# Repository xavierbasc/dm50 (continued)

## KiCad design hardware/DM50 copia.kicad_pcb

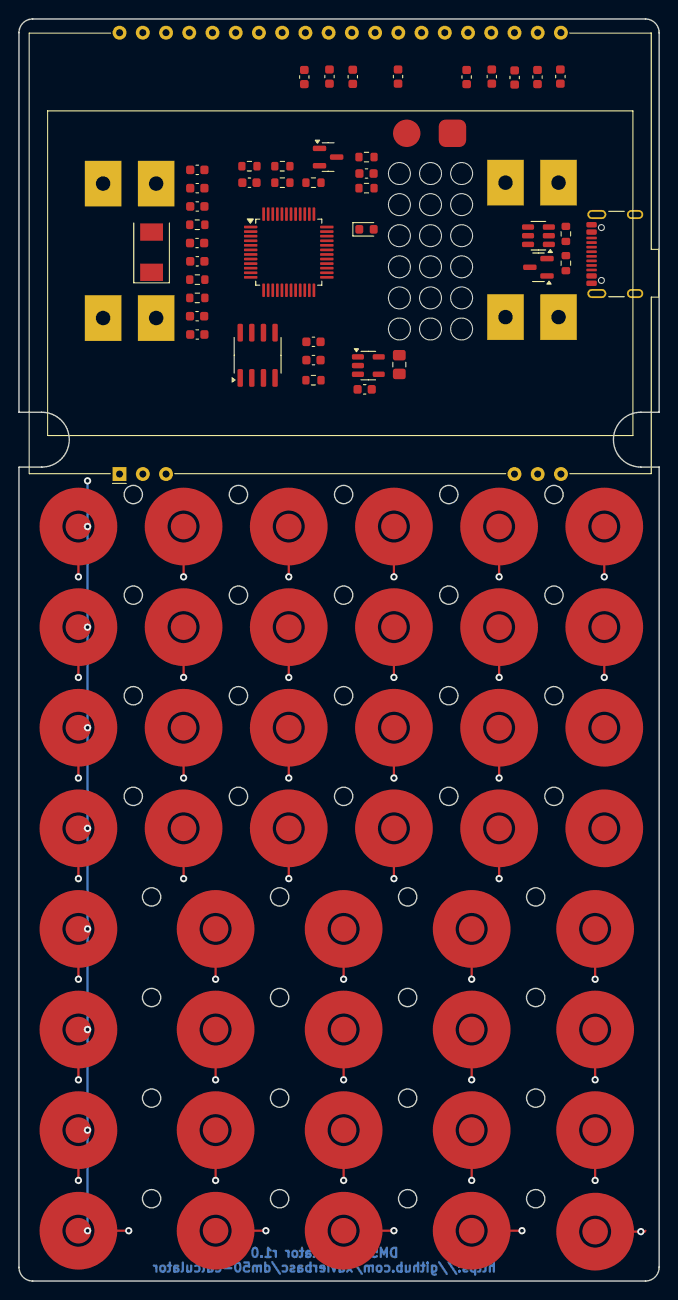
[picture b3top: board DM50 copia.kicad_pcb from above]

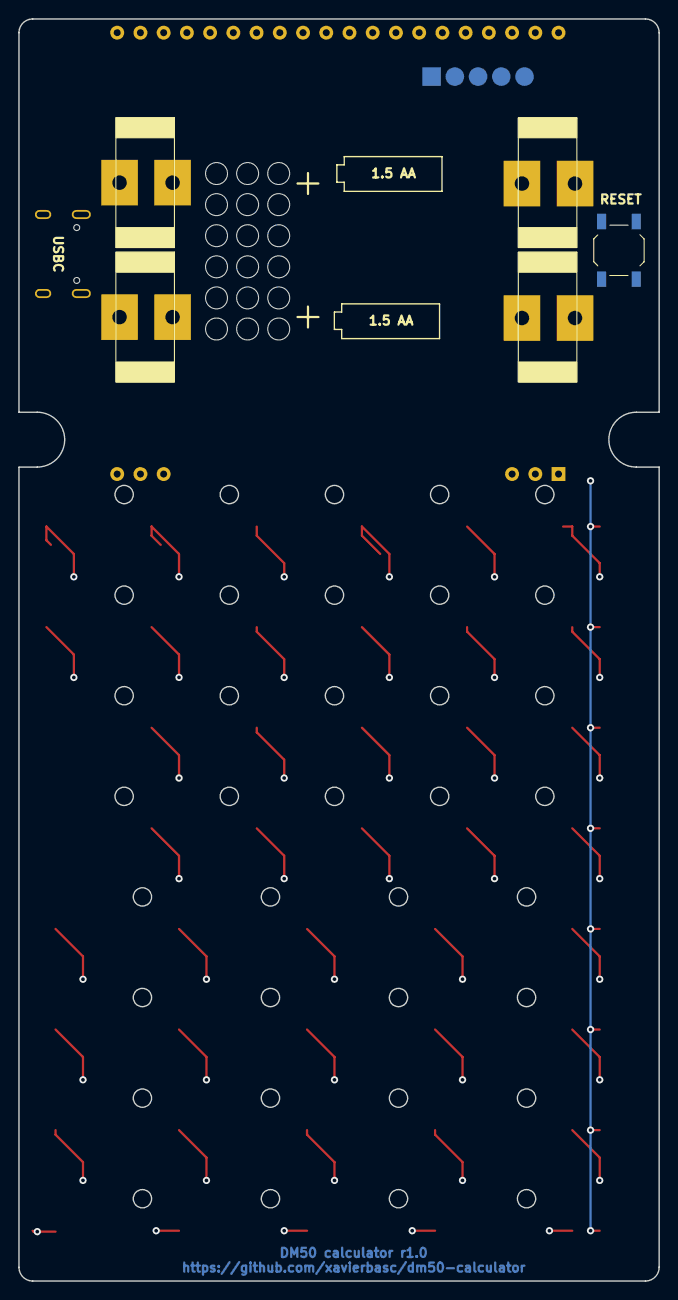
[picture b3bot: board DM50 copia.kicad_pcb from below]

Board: 2 copper layers, 70.0 x 138.0 mm, 93 parts (4 on the bottom side), 63 nets.

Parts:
BT1, BT2: AA; dm50-batAA
BZ1: Buzzer
C1, C2, C3, C4, C5, C6, C7, C8, C9: 1uF; C_0603_1608Metric
C10, C12, C14, C15, C16, C17: 100nF; C_0603_1608Metric
C11, C13: 22pF; C_0603_1608Metric
C18, C20: 4.7 uF; C_0603_1608Metric
C19: 10 uF; C_0603_1608Metric
C21: 2.2uF; C_0603_1608Metric
D1: LED (RED); LED_0603_1608Metric
D2: BAT54C; SOT-23
J1: ST-LINK; JST_CON_SMD
J2: USB_C_Receptacle_USB2.0_14P; USB_C_Receptacle_GCT_USB4105-xx-A_16P_TopMnt_Horizontal
L1: 1uH; L_0805_2012Metric_Pad1.15x1.40mm_HandSolder
Q1: MMBT3904; SOT-23
R1: 10k; R_0603_1608Metric
R2, R10, R11: 5.1K; R_0603_1608Metric
R3, R6: 1M; R_0603_1608Metric
R4, R12: 10K; R_0603_1608Metric
R5, R7: 100K; R_0603_1608Metric
R8, R9: R; R_0603_1608Metric
SW1: F1; dm50-button
SW2: F2; dm50-button
SW3: F3; dm50-button
SW4: F4; dm50-button
SW5: F5; dm50-button
SW6: F6; dm50-button
SW7: E+; dm50-button
SW8: 1/x; dm50-button
SW9: SQR; dm50-button
SW10: LOG; dm50-button
SW11: LN; dm50-button
SW12: XEQ; dm50-button
SW13: STO; dm50-button
SW14: RCL; dm50-button
SW15: R; dm50-button
SW16: SIN; dm50-button
SW17: COS; dm50-button
SW18: TAN; dm50-button
SW19, SW20: ENTER; dm50-button
SW21: x<>y; dm50-button
SW22: +/-; dm50-button
SW23: E; dm50-button
SW24: DEL; dm50-button
SW25: UP; dm50-button
SW26: 7; dm50-button
SW27: 8; dm50-button
SW28: 9; dm50-button
SW29: /; dm50-button
SW30: DOWN; dm50-button
SW31: 4; dm50-button
SW32: 5; dm50-button
SW33: 6; dm50-button
SW34: x; dm50-button
SW35: OPT; dm50-button
SW36: 1; dm50-button
SW37: 2; dm50-button
SW38: 3; dm50-button
SW39: -; dm50-button
SW40: ON; dm50-button
SW41: 0; dm50-button
SW42: .; dm50-button
SW43: =; dm50-button
SW44: +; dm50-button
SW45: SW_RESET; SW_SPST_TL3342
U1: EA_DOGL128X-6; EA_DOGL128-6
U2: STM32U535CBT6; LQFP-48_7x7mm_P0.5mm
U3: AT25SF641; SOIC-8_3.9x4.9mm_P1.27mm
U4: USBLC6-2SC6; SOT-23-6
U5: ADP2108AUJ-3.3; TSOT-23-5
Y1: HSE 16MHz; Crystal_SMD_0603-2Pin_6.0x3.5mm

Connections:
3.3V: BZ1.1 (+), C14.1, C15.1, C16.1, C17.1, C18.1, C19.1, L1.2, R1.1, R4.2, R8.1, U1.34 (VDD2), U1.35 (VDD), U2.1 (VBAT), U2.9 (VDDA), U2.24 (VDD), U2.36 (VDD), U2.48 (VDD), U3.8 (VCC), U5.4 (FB)
BOOT0: R7.2, SW30.2, SW31.2, SW32.2, SW33.2, SW34.2, U2.44 (PH3)
BUZZER: R9.1, U2.42 (PB6)
COL01: SW1.1, SW7.1, SW13.1, SW19.1, SW25.1, SW30.1, SW35.1, SW40.1, U2.3 (PC14)
COL02: R4.1, SW2.1, SW8.1, SW14.1, SW20.1, SW26.1, SW31.1, SW36.1, SW41.1, U2.40 (PB4)
COL03: SW3.1, SW9.1, SW15.1, SW21.1, SW27.1, SW32.1, SW37.1, SW42.1, U2.30 (PA9)
COL04: SW4.1, SW10.1, SW16.1, SW22.1, SW28.1, SW33.1, SW38.1, SW43.1, U2.20 (PB2)
COL05: SW5.1, SW11.1, SW17.1, SW23.1, SW29.1, SW34.1, SW39.1, SW44.1, U2.29 (PA8)
COL06: SW6.1, SW12.1, SW18.1, SW24.1, U2.38 (PA15)
DISP_A0: U1.38 (A0), U2.14 (PA4)
DISP_CS1B: U1.40 (~CS1B), U2.15 (PA5)
DISP_RST: U1.39 (~RST), U2.31 (PA10)
DISP_SCL: U1.37 (SCL), U2.12 (PA2)
DISP_SI: U1.36 (SI), U2.43 (PB7)
GND: BT2.2 (-), C1.2, C2.2, C3.2, C5.2, C6.2, C8.1, C10.2, C11.2, C12.2, C13.2, C14.2, C15.2, C16.2, C17.2, C18.2, C19.2, C20.2, C21.2, D1.1 (K), J1.1, J2.A1 (GND), J2.A12 (GND), J2.B1 (GND), J2.B12 (GND), J2.S1 (SHIELD), Q1.2 (E), R5.2, R6.1, R7.1, R10.2, R11.2, SW45.1, U1.26 (VSS), U1.33 (VSS), U2.8 (VSSA), U2.23 (VSS), U2.35 (VSS), U2.47 (VSS), U3.4 (GND), U4.2 (GND), U5.2 (GND)
LED01: R2.1, U2.41 (PB5)
NRST: C10.1, J1.5, R1.2, U2.7 (NRST)
unnamed: BT1.2 (-), BT2.1 (+)
unnamed: BZ1.2 (-), Q1.3 (C), R8.2
unnamed: D1.2 (A), R2.2
unnamed: J2.A5 (CC1), R10.1
unnamed: J2.B5 (CC2), R11.1
unnamed: J2.A6 (D+), J2.B6 (D+), U4.3 (I/O2)
unnamed: J2.A7 (D-), J2.B7 (D-), U4.1 (I/O1)
unnamed: Q1.1 (B), R9.2
unnamed: C4.2, C7.2, U1.30 (CAP1N)
unnamed: C4.1, U1.29 (CAP1P)
unnamed: C9.1, U1.27 (CAP2N)
unnamed: C9.2, U1.28 (CAP2P)
unnamed: C7.1, U1.31 (CAP3P)
unnamed: C1.1, U1.21 (V0)
unnamed: C2.1, U1.22 (V1)
unnamed: C3.1, U1.23 (V2)
unnamed: C5.1, U1.24 (V3)
unnamed: C6.1, U1.25 (V4)
unnamed: C8.2, U1.32 (VOUT)
unnamed: D2.2, J2.A4 (VBUS), J2.A9 (VBUS), J2.B4 (VBUS), J2.B9 (VBUS), U4.5 (VBUS)
unnamed: R12.2, SW45.2, U5.3 (EN)
unnamed: L1.1, U5.5 (SW)
unnamed: C20.1, D2.3, R12.1, U5.1 (Vin)
OSCIN: C11.1, U2.5 (PH0), Y1.2
OSCOUT: C13.1, U2.6 (PH1), Y1.1
QUADSPI_CLK: U2.13 (PA3), U3.6 (CLK)
QUADSPI_IO0: U2.19 (PB1), U3.5 (DI(IO0))
QUADSPI_IO1: U2.18 (PB0), U3.2 (DO(IO1))
QUADSPI_IO2: U2.17 (PA7), U3.3 (IO2)
QUADSPI_IO3: U2.16 (PA6), U3.7 (IO3)
QUADSPI_NCS: U2.10 (PA0), U3.1 (~CS)
ROW01: SW1.2, SW2.2, SW3.2, SW4.2, SW5.2, SW6.2, U2.26 (PB13)
ROW02: SW7.2, SW8.2, SW9.2, SW10.2, SW11.2, SW12.2, U2.45 (PB8)
ROW03: SW13.2, SW14.2, SW15.2, SW16.2, SW17.2, SW18.2, U2.46 (PB9)
ROW04: SW19.2, SW20.2, SW21.2, SW22.2, SW23.2, SW24.2, U2.21 (PB10)
ROW05: SW25.2, SW26.2, SW27.2, SW28.2, SW29.2, U2.25 (PB12)
ROW07: SW35.2, SW36.2, SW37.2, SW38.2, SW39.2, U2.27 (PB14)
ROW08/WAKEUP: R5.1, SW40.2, SW41.2, SW42.2, SW43.2, SW44.2
SWD_SWCLK: J1.3, U2.37 (PA14)
SWD_SWDIO: J1.2, U2.34 (PA13)
SWD_SWO: J1.4, U2.39 (PB3)
USB_DM (D-): U2.32 (PA11), U4.6 (I/O1)
USB_DP (D+): U2.33 (PA12), U4.4 (I/O2)
VBAT: BT1.1 (+), R3.2
VBAT_SNS: C12.1, R3.1, R6.2, U2.11 (PA1)
VCAP1: C21.1, U2.22 (VCAP)

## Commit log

2023-01-07 initial file creation
2023-01-07 Update README.md
    Readme changes
2023-01-12 Paths changes
2023-01-12 directory structure
2023-01-12 Hardware DM50
2023-01-12 Create LICENSE
2023-01-13 SCH changes
2024-03-31 electronic design advances
2024-03-31 Readme.md changes
2024-03-31 Add pdf schema
2024-03-31 Global changes
2024-03-31 Show schema image
2024-03-31 Actualizar README.md
2024-03-31 Shematic changes
2024-03-31 structure changes
2024-03-31 img changes
2024-04-02 Schema updates
2024-04-02 images changes
2024-04-02 new MCU image
2024-04-02 new files
2024-04-03 update 3d render
2024-04-03 include PCB image
2024-04-04 3d case init
2024-04-04 new image
2024-04-04 pcb changes
2024-04-04 3d case changes
2024-04-27 git changes
2024-04-27 pcb and rendeer
2024-04-27 upgrade image
2024-05-01 keyboard changes
2024-05-01 3d changes
2024-05-02 3d render
2024-05-03 crystal change
2024-05-07 upgrade readme.md
2024-05-07 Faceplate init
2024-05-17 case changes
2024-05-25 3d case
2024-06-05 create website
2024-06-05 update gitignore
2024-06-05 gem changes
2024-06-11 remove website
2024-06-18 add nuts
2024-06-30 3d changes (step files)
2024-07-13 LiPO CONNECTOR
2024-07-14 imgs changes
2024-07-30 LiPO charging sensor
2024-08-01 update schema
2024-08-01 imgs pcb
2024-08-03 housing changes
2024-08-04 remove files
2024-08-06 keys
2024-08-10 add jtag connector
2024-08-10 JTAG connector
2024-08-12 update case image
2024-08-13 DM50 V1
2024-08-14 bezel develop
2024-08-16 STM32U575RIT6 change
2024-08-17 corrections
2024-08-21 pcb updates
2024-08-22 pcb upgrades
2024-08-23 pcb upgrade
2024-08-25 update images
2024-08-26 case upgrade
2024-08-26 bezel changes
2024-08-30 case upgrades
2024-09-10 texture case
2024-09-10 case texture
2024-09-19 case 3d
2024-09-21 3d case
    3d case
2024-11-09 Added protection resistors against overvoltage on USART ports (thanks to Ruber Aparicio).
2024-11-15 LCD port bugfix
2024-12-17 3D case V3
2024-12-21 3d case upgrade
2024-12-27 upgrade 3d detail
2025-01-04 upgrade 3d
2025-01-05 readme: Fix link for DB48x project
    The link was incorrectly pointing to the C47 project's web page.
